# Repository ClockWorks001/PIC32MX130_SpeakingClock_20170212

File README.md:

# PIC32MX130F Speaking Clock Project.
---
## Description

This is a Speaking Clock project with [PIC32MX130 micro controller][2] with [MPLAB.X][3] [MCC][4].
I have created this project using Mr.ChaN's wonderful FatFs program. 
You can operat it by terminal with serial communication speed of 115,200 bps.

References.
<http://elm-chan.org/fsw/ff/00index_e.html> 
<http://microchip.wikidot.com/swtools:start> 

## Prerequisites

I created this project using the free versions of the following tools:
 * [FatFs][1] (R0.12b)
 * [Microchip MPLAB X][3] (v3.51)
 * [Microchip MPLAB X Code Configurator][4] (v3.26.2)
 * [Microchip XC32 Compiler][5] (v1.42)
 * [KiCad][6] (v4.0.1)
 * [Jw_cad][8] (v8.0.3a)

You shoud download and install these tools appropriately before you will open this project and build it.
I use the [Microchip MPLAB PICkit3 In-Circuit Debugger][7] to program the chip and debug it.  

Also, I use the [KiCad][6] to draw the electric circuit schematic.

## Licence

[MIT](https://github.com/tcnksm/tool/blob/master/LICENCE)

## Author

Hiroshi Murakami  
<https://github.com/ClockWorks001>  

[1]: http://elm-chan.org/fsw/ff/00index_e.html "FatFs"
[2]: http://ww1.microchip.com/downloads/en/DeviceDoc/60001168F.pdf "PIC32MXxxx"
[3]: http://www.microchip.com/pagehandler/en-us/family/mplabx/ "MPLAB X"
[4]: http://www.microchip.com/mplab/mplab-code-configurator "MPLAB Code Configurator "
[5]: http://www.microchip.com/pagehandler/en_us/devtools/mplabxc/ "MPLAB XC Compilers"
[6]: http://kicad-pcb.org/ "KiCad"
[7]: http://www.microchip.com/Developmenttools/ProductDetails.aspx?PartNO=PG164130 "MPLAB PICkit3 In-Circuit Debugger"
[8]: http://www.jwcad.net/ "Jw_cad"

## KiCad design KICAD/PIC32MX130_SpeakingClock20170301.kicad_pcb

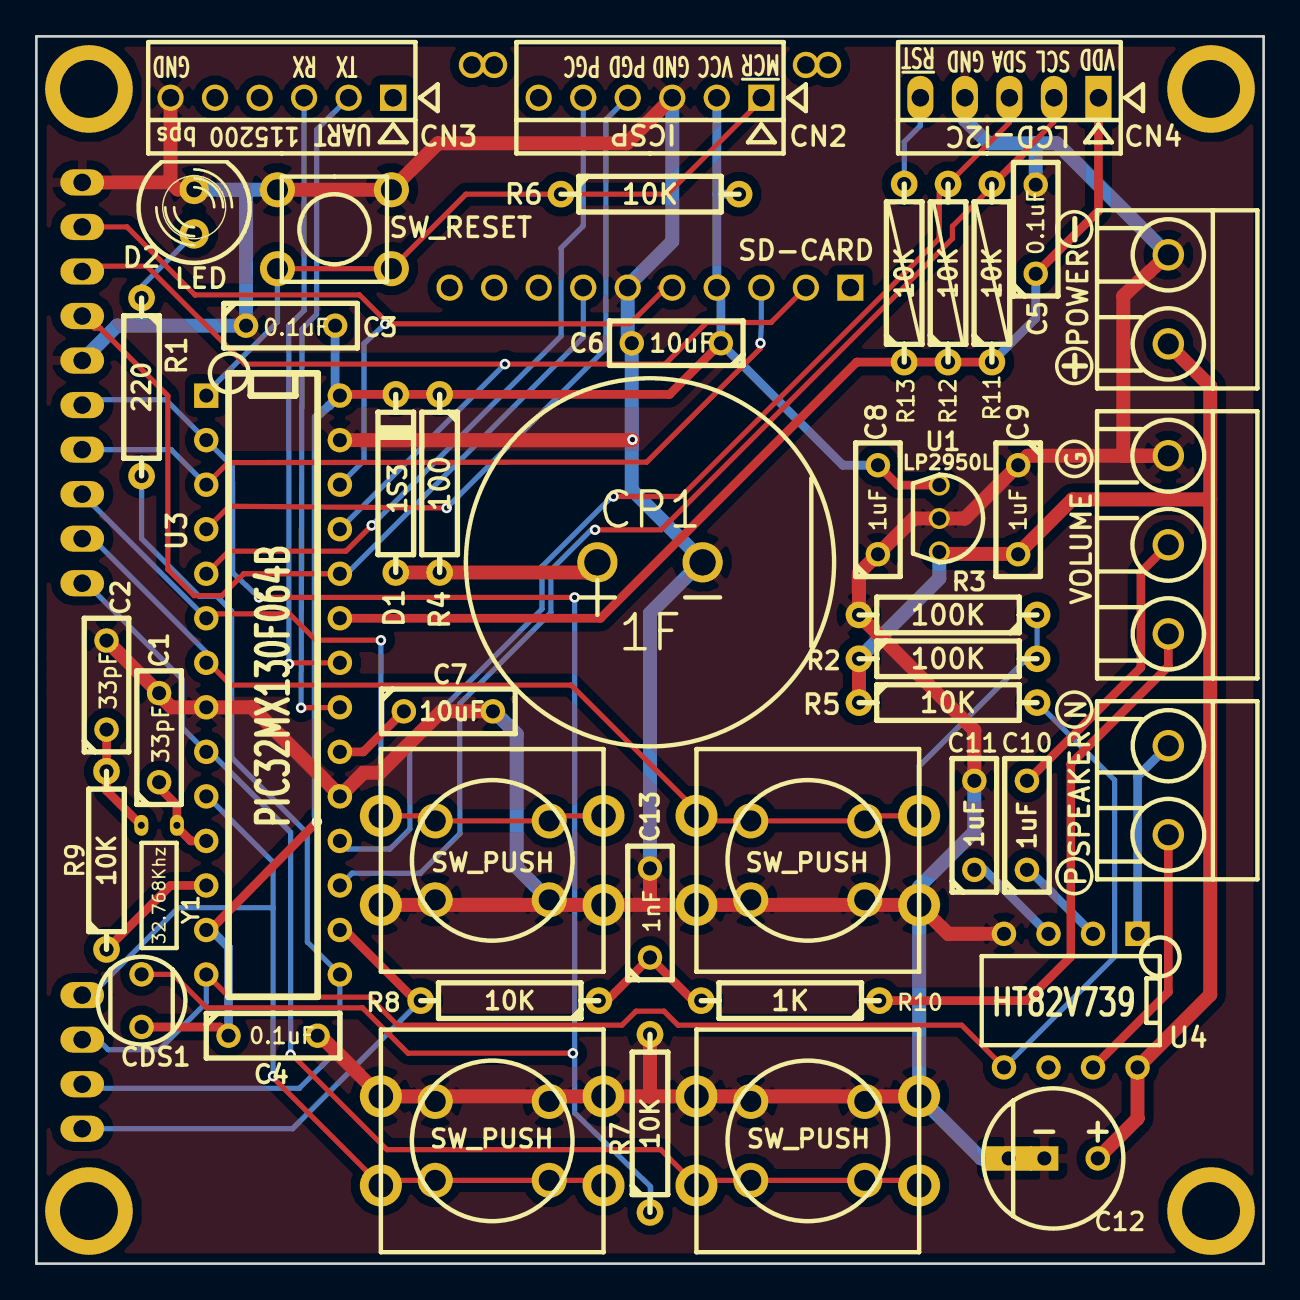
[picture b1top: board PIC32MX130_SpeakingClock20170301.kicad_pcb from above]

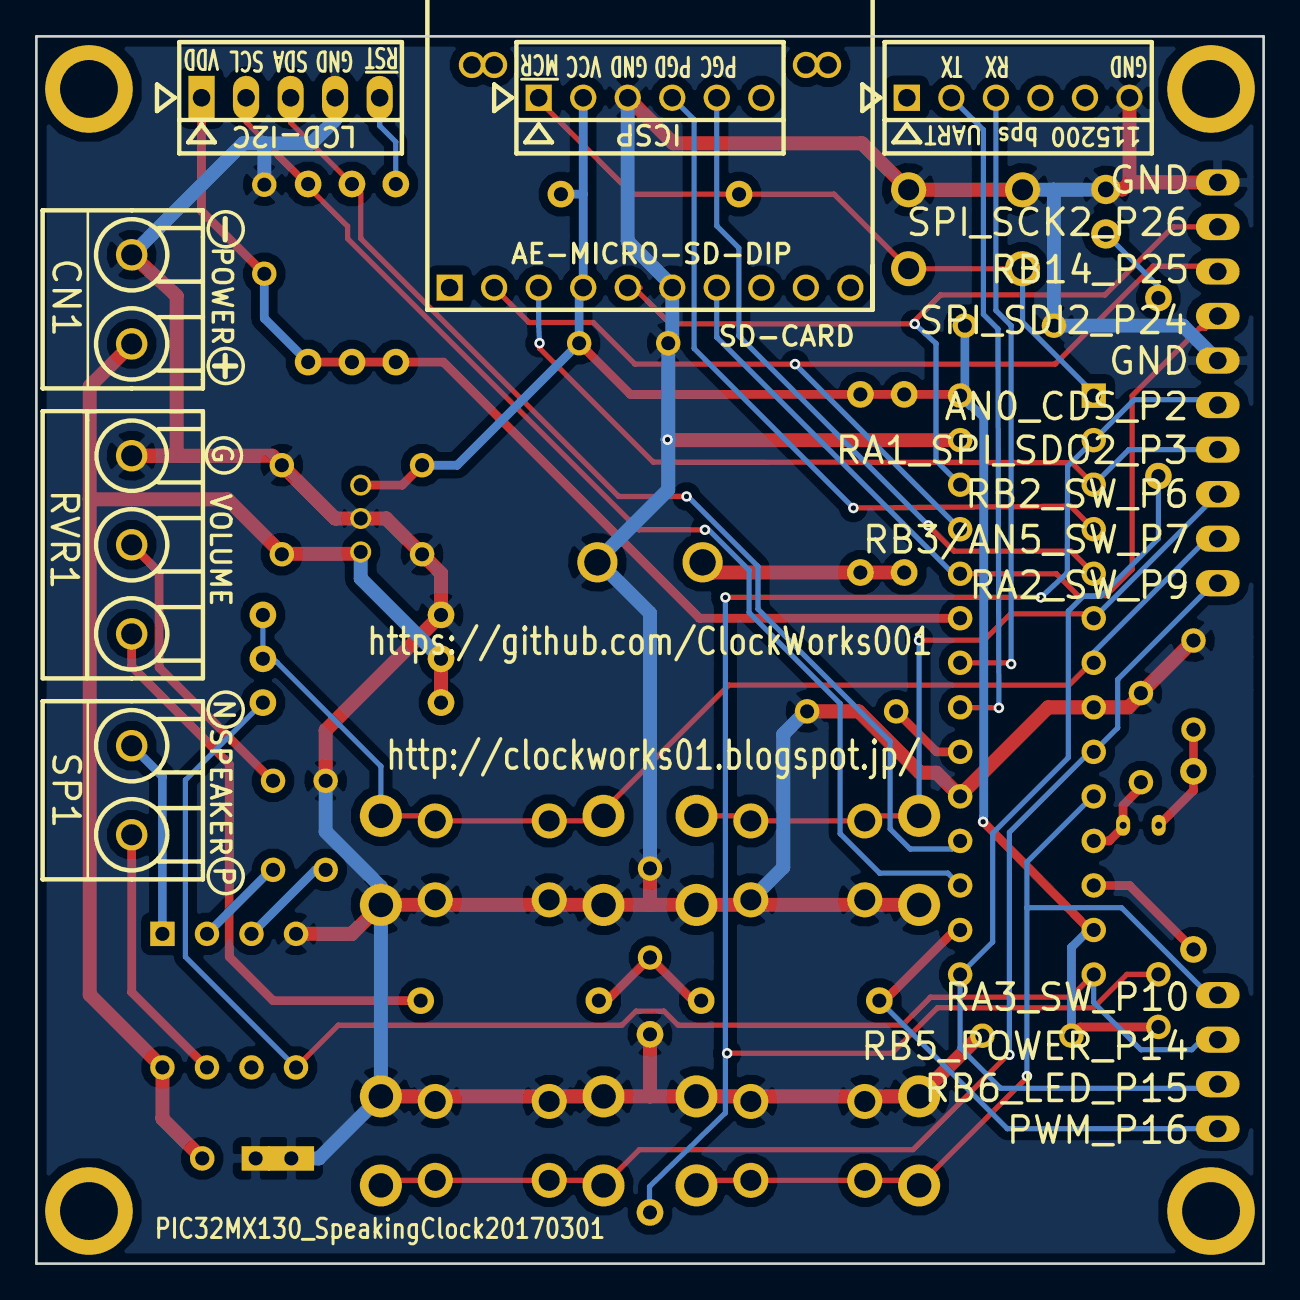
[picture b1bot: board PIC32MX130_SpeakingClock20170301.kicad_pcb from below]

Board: 2 copper layers, 70.0 x 70.0 mm, 64 parts (18 on the bottom side), 37 nets.

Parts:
C1, C2: 33pF; C2_MU
C3, C4, C5: 0.1uF; C2_MU
C6, C7: 10uF; C2_MU
C8, C9, C10, C11: 1uF; C2_MU
C12: 10uF; CP2_MU
C13: 1nF; C2_MU
CDS1: 10-20K/1M; CDS_5mm
CN1: CN-POWER; TERMINAL_2P
CN2: CN-ICSP; PINHEAD1-6_MU
CN3: CN-UART-FTDI-TTL-232R-3V3; PINHEAD1-6_MU
CN4: LCD_I2C_AQM1602XA-RN-GBW; PINHEAD1-5_MU2
CP1: 1F; C_SE-5R5
D1: 1S3; D4_MU
D2: LED; LED-5MM_AK
PAD1: AN0_CDS_P2; PAD1mmX1.5mmX2.5mm
PAD2: RA1_SPI_SDO2_P3; PAD1mmX1.5mmX2.5mm
PAD3: RB2_SW_P6; PAD1mmX1.5mmX2.5mm
PAD4: RB3/AN5_SW_P7; PAD1mmX1.5mmX2.5mm
PAD5: RA2_SW_P9; PAD1mmX1.5mmX2.5mm
PAD6: RA3_SW_P10; PAD1mmX1.5mmX2.5mm
PAD7: RB5_POWER_P14; PAD1mmX1.5mmX2.5mm
PAD8: RB6_LED_P15; PAD1mmX1.5mmX2.5mm
PAD9: PWM_P16; PAD1mmX1.5mmX2.5mm
PAD10: SPI_SDI2_P24; PAD1mmX1.5mmX2.5mm
PAD11: RB14_P25; PAD1mmX1.5mmX2.5mm
PAD12: SPI_SCK2_P26; PAD1mmX1.5mmX2.5mm
PAD13, PAD14: GND; PAD1mmX1.5mmX2.5mm
PAD15, PAD16, PAD17, PAD18: PAD; PAD3mmX5mm
R1: 220; R4_MU
R2, R3: 100K; R4_MU
R4: 100; R4_MU
R5, R6, R7, R8, R9, R11, R12, R13: 10K; R4_MU
R10: 1K; R4_MU
RVR1: 10K; TERMINAL_3P
SDC1: AE-MICRO-SD-DIP; SD_CARD_AE-MICRO-SD-DIP
SP1: SPEAKER; TERMINAL_2P
SW1, SW2, SW3, SW4: SW_PUSH; SW_PUSH-12mm+_AK
SW_RESET1: SW_RESET; SW_PUSH-6mm_AK
U1: LP2950L; TO92
U3: PIC32MX130F064B; DIP-28_300_MU
U4: HT82V739; DIP-8_300_MU
Y1: 32.768Khz; X_TAL_VT200

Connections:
+3.3V: C3.2, C4.1, C6.1, C8.2, CDS1.1, CN2.2, D1.1, R4.1, R6.2, SDC1.4, U1.1, U3.13, U3.28
+5.0V: C9.2, C12.1, CN1.1, R2.1, R5.1, U1.3, U4.8
GND: C1.2, C2.2, C3.1, C4.2, C5.2, C6.2, C7.2, C8.1, C9.1, C11.2, C12.2, C13.2, CN1.2, CN2.3, CN3.6, CN4.4, CP1.2, D2.2, PAD13.1, PAD14.1, R3.2, R7.2, RVR1.3, SDC1.6, SW1.1, SW2.1, SW3.1, SW4.1, SW_RESET1.1, U1.2, U3.8, U3.19, U3.27, U4.4
unnamed: C1.1, U3.11, Y1.1
unnamed: C2.1, R9.2, Y1.2
unnamed: C5.1, CN4.1, R11.1, R12.1, R13.1, U3.23
unnamed: C7.1, U3.20
unnamed: C10.1, U4.2
unnamed: C10.2, RVR1.2
unnamed: C11.1, U4.3
unnamed: C13.1, R8.1, R10.2
unnamed: CN2.1, R6.1, SW_RESET1.2, U3.1
unnamed: CN2.4, U3.4
unnamed: CN2.5, U3.5
unnamed: CN3.2, U3.21
unnamed: CN3.3, U3.22
unnamed: CN4.2, R11.2, U3.17
unnamed: CN4.3, R12.2, U3.18
unnamed: CN4.5, R13.2
unnamed: CP1.1, D1.2, R4.2
unnamed: D2.1, R1.1
unnamed: R9.1, U3.12
unnamed: R10.1, RVR1.1
unnamed: SP1.1, U4.1
unnamed: SP1.2, U4.7
P2_AN0_CDS: CDS1.2, PAD1.1, R7.1, U3.2
P3_RA1_SPI_SDO2: PAD2.1, SDC1.3, U3.3
P6_RB2_SW1: PAD3.1, SW1.2, U3.6
P7_RB3/AN5_SW2: PAD4.1, R2.2, R3.1, SW2.2, U3.7
P9_RA2_SW3: PAD5.1, SW3.2, U3.9
P10_RA3_SW4: PAD6.1, SW4.2, U3.10
P14_RB5_POWER: PAD7.1, R5.2, U3.14, U4.5
P15_RB6_LED: PAD8.1, R1.2, U3.15
P16_PWM: PAD9.1, R8.2, U3.16
P24_SPI_SDI2: PAD10.1, SDC1.7, U3.24
P25_RB14: PAD11.1, SDC1.2, U3.25
P26_SPI_SCK2: PAD12.1, SDC1.5, U3.26

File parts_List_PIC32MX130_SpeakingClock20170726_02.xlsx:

| Source | C:/Users/mura01/Dropbox/20170212_SpeakingClock_PIC32MX130/KICAD/PIC32MX130_Spea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
 | Kicad Rev | Eeschema 4.0.1-stable
 | Generated Date | 2017/07/26 8:39:37
 | Title | Not Set
 | Company | Not Set
 | Revision | Not Set
 | Date Issue | Not Set
No. | Reference | Value | Library | Library Ref | Item |  | Pieces | Price
1 | C1 | 33pF | mylib20161223 | C | 33pF
2 | C2 | 33pF | mylib20161223 | C | 33pF |  | 2 | 10 | 20
3 | C3 | 0.1uF | mylib20161223 | C | 0.1uF
4 | C4 | 0.1uF | mylib20161223 | C | 0.1uF
5 | C5 | 0.1uF | mylib20161223 | C | 0.1uF |  | 3 | 10 | 30
6 | C6 | 10uF | mylib20161223 | C | 10uF
7 | C7 | 10uF | mylib20161223 | C | 10uF |  | 2 | 20 | 40
8 | C8 | 1uF | mylib20161223 | C | 1uF
9 | C9 | 1uF | mylib20161223 | C | 1uF
10 | C10 | 1uF | mylib20161223 | C | 1uF
11 | C11 | 1uF | mylib20161223 | C | 1uF |  | 4 | 10 | 40
12 | C12 | 10uF | mylib20161223 | CP | 10uF |  | 1 | 10 | 10
13 | C13 | 1nF | mylib20161223 | C | 1nF |  | 1 | 10 | 10
14 | CP1 | 1F | mylib20161223 | CP | 1F |  | 1 | 100 | 100
15 | D1 | 1S3 | mylib20161223 | D_Schottky | 1S3 |  | 1 | 13 | 13
16 | D2 | LED | mylib20161223 | LED | LED |  | 1 | 20 | 20
17 | R1 | 220 | mylib20161223 | R | 220 |  | 1 | 1 | 1
18 | R2 | 100K | mylib20161223 | R | 100K
19 | R3 | 100K | mylib20161223 | R | 100K |  | 2 | 1 | 2
20 | R10 | 1K | mylib20161223 | R | 1K |  | 1 | 1 | 1
21 | R4 | 100 | mylib20161223 | R | 100 |  | 1 | 1 | 1
22 | R5 | 10K | mylib20161223 | R | 10K
23 | R6 | 10K | mylib20161223 | R | 10K
24 | R7 | 10K | mylib20161223 | R | 10K
25 | R8 | 10K | mylib20161223 | R | 10K
26 | R9 | 10K | mylib20161223 | R | 10K
27 | R11 | 10K | mylib20161223 | R | 10K
28 | R12 | 10K | mylib20161223 | R | 10K
29 | R13 | 10K | mylib20161223 | R | 10K |  | 8 | 1 | 8
30 | SW1 | SW_PUSH | mylib20161223 | SW_PUSH | SW_PUSH
31 | SW2 | SW_PUSH | mylib20161223 | SW_PUSH | SW_PUSH
32 | SW3 | SW_PUSH | mylib20161223 | SW_PUSH | SW_PUSH
33 | SW4 | SW_PUSH | mylib20161223 | SW_PUSH | SW_PUSH
34 | SW_RESET1 | SW_RESET | mylib20161223 | SW_PUSH | SW_PUSH |  | 5 | 10 | 50
35 | U1 | LP2950L | mylib20161223 | XC6202 | LP2950L-3.3V | I-08749 | 1 | 20 | 20
36 | U3 | PIC32MX130F064B | mylib20161223 | PIC32MX130F064B | PIC32MX130F064B |  | 1 | 350 | 350
37 |  |  |  |  | IC_SOCKET 28P | P-00013 | 1 | 20 | 20
38 | U4 | HT82V739 | mylib20161223 | HT82V739 | HT82V739 | I-02796 | 1 | 50 | 50
39 |  |  |  |  | IC_SOCKET_8P | P-00017 | 1 | 10 | 10
40 | Y1 | 32.768Khz | device | Crystal | VT-200 | P-04005 | 1 | 30 | 30
41 |  |  |  |  | TUBE 2mmX5mm |  | 1
42 | SDC1 | AE-MICRO-SD-DIP | mylib20161223 | AE-MICRO-SD-DIP | AE-MICRO-SD-DIP | K-05488 | 1 | 300 | 300
43 | CDS1 | 10-20K/1M | mylib20161223 | Photores | CDS GL5528 | I-05886 | 1 | 25 | 25
44 |  |  |  |  | TUBE 2mmX10mm |  | 2
45 | CN1 | CN-POWER | mylib20161223 | CN-POWER | TERMINAL 2P | P-01306 | 1 | 20 | 20
46 |  |  |  |  | BATTERY CASE | P-02671 | 1 | 70 | 70
47 | CN2 | CN-ICSP | mylib20161223 | CN-ICSP | PIN HEAD 1X6 | C-01669 | 1 | 20 | 20
48 | CN3 | CN-UART-FTDI-TTL-232R-3V3 | mylib20161223 | CN-UART-601-Arduino | PIN HEAD 1X6 | C-01669 | 1 | 20 | 20
49 | CN4 | LCD_I2C_AQM1602XA-RN-GBW | mylib20161223 | LCD_I2C_AQM1602XA-RN-GBW | AQM1602XA-RN-GBW | K-08896 | 1 | 550 | 550
50 |  |  |  |  | PIN HEAD 1X4 | C-03950 | 1 | 3 | 3
51 |  |  |  |  | コネクタハウジング 1X4 | C-12153 | 1 | 10 | 10
52 |  |  |  |  | コネクタ端子 | C-12160 | 4 | 5 | 20
53 |  |  |  |  | WIRE |  | 4
54 | SP1 | SPEAKER | mylib20161223 | SPEAKER | SPEAKER | P-06275 | 1 | 300 | 300
55 |  |  |  |  | TERMINAL 2P | P-01306 | 1 | 20 | 20
56 |  |  |  |  | WIRE |  | 2
57 | RVR1 | 10K | mylib20161223 | RVR | VOLUME(10KΩA) | P00242 | 1 | 40 | 40
 |  |  |  |  | KNOB(ツマミ) 15mm | P-00253 | 1 | 20 | 20
58 |  |  |  |  | TERMINAL 3P | P-01307 | 1 | 30 | 30
59 |  |  |  |  | WIRE(THIN)] |  | 3
60 | BOARD |  |  |  | PRINT BOARD |  | 1 | 300 | 300
61 | (MICRO SD CARD) |  |  |  | (MICRO SD CARD) |  | -
62 | (BATTERY) |  |  |  | (BATTERY) |  | -
63 | ケース | 3mm厚シナベニヤ、切り出し | JW_CAD |  | 3mm厚シナベニヤ、切り出し |  | 2 | 285 | 570
64 | ネジ | 直径3mmタッピングネジ | - |  | - |  | 8 | 5 | 40
 |  |  |  |  | total |  | 81 | - | 3184

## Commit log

2017-08-27 rm SpeachNote
2017-08-28 amend operation instructions
2017-09-18 add a operation manual.
2017-09-18 amend a operational manual.
2018-01-01 amend spi2-DI pin to pull up. it needs for SD card output
2018-01-01 amended documents about SPI DI pull up.
2018-01-01 check
2018-01-01 amend SPI DI pin for pulling up. it needs for SD card DO. chek2
